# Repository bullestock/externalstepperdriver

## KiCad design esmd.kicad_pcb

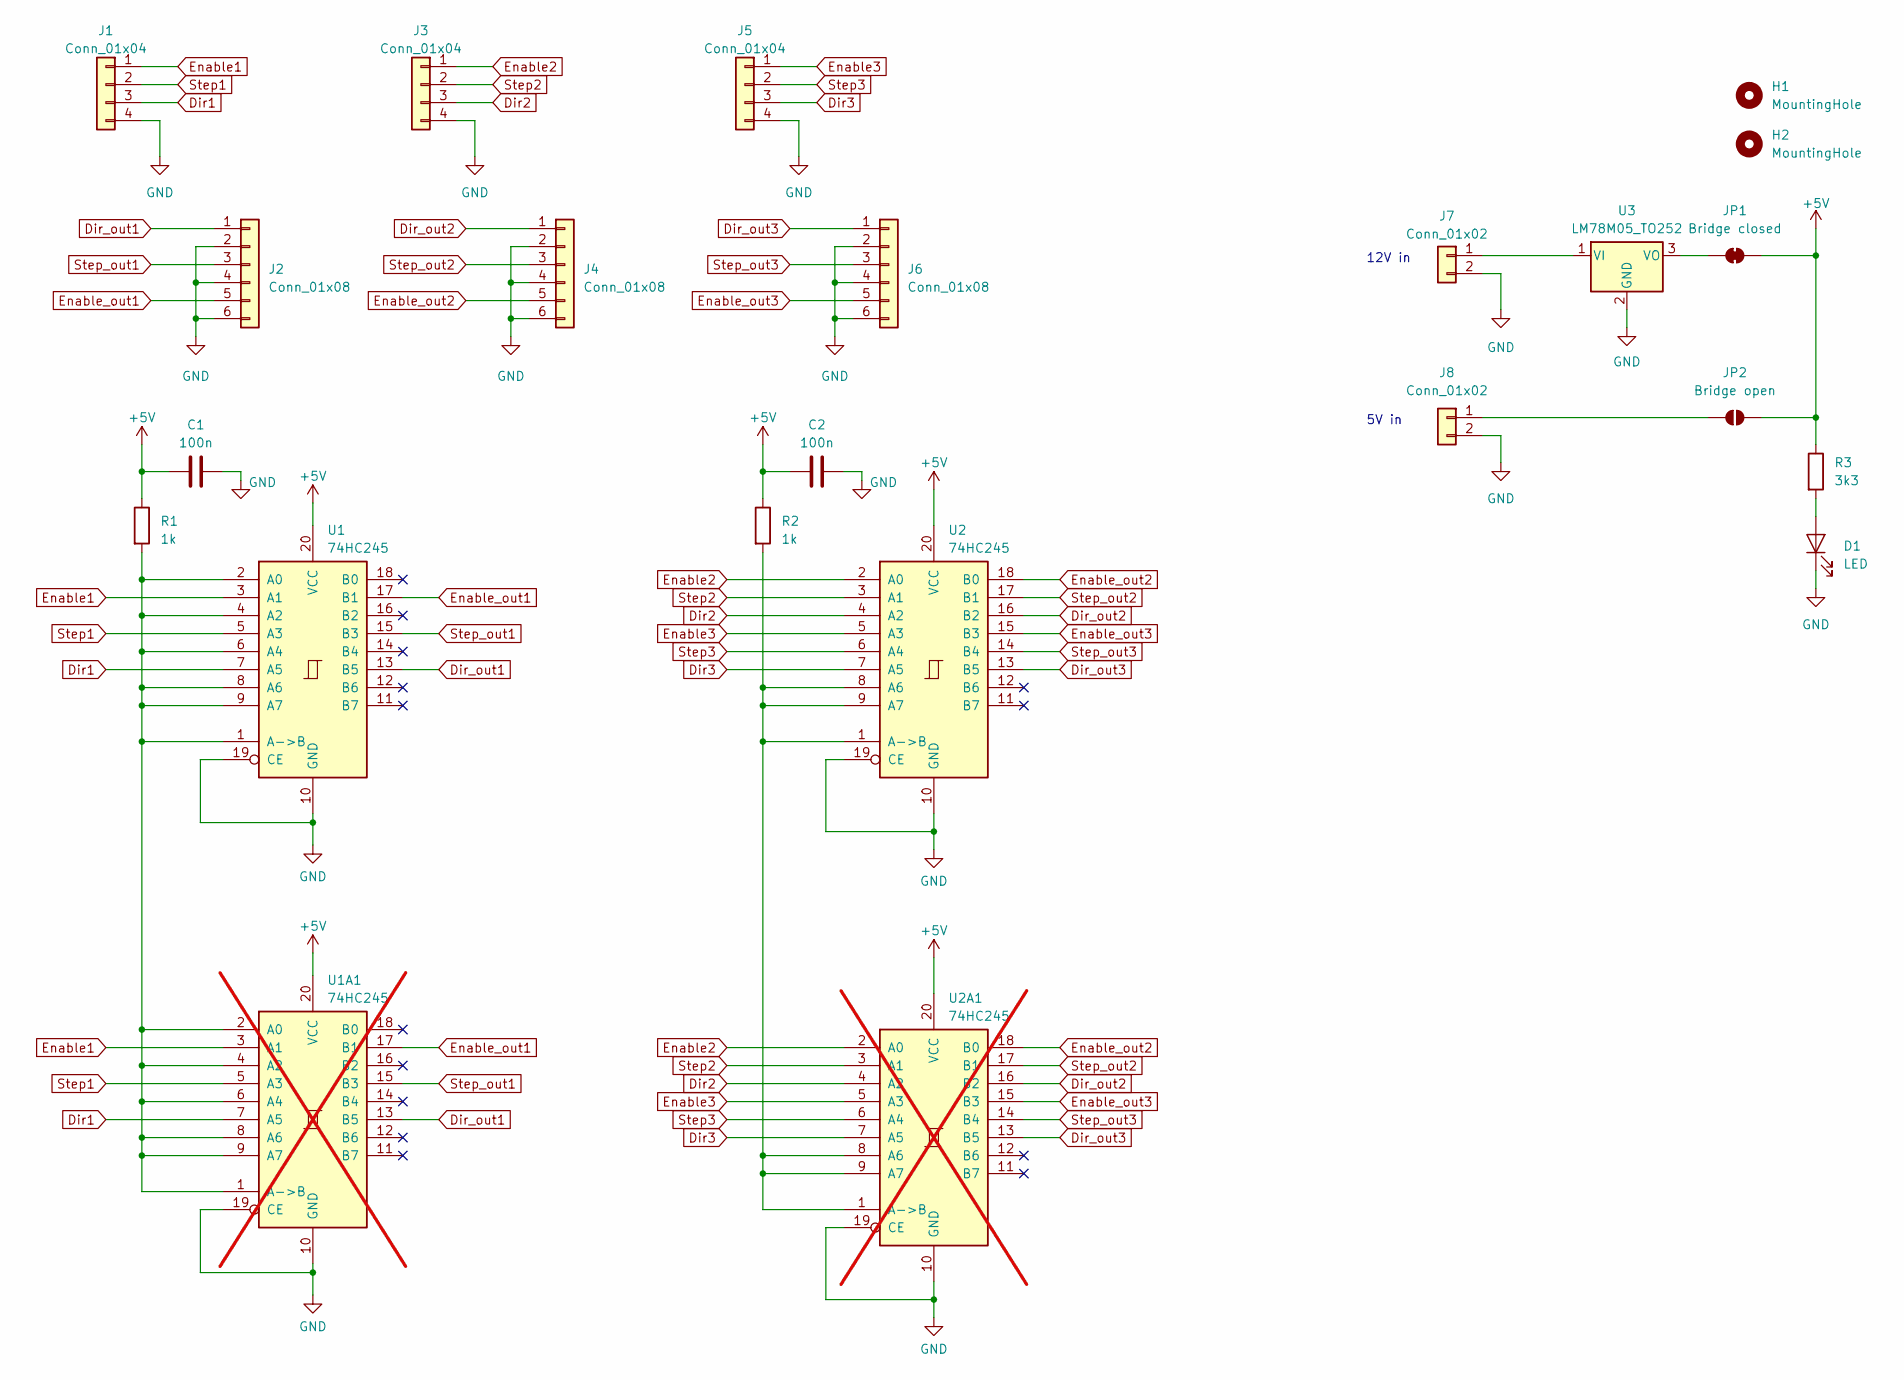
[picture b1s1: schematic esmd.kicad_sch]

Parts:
C1, C2: 100n; C_0603_1608Metric
D1: LED; LED_0603_1608Metric
H1, H2: MountingHole; MountingHole_3.2mm_M3
J1, J3, J5: Conn_01x04; JST_XH_B4B-XH-A_1x04_P2.50mm_Vertical
J2, J4, J6: Conn_01x08; JST_XH_B6B-XH-A_1x06_P2.50mm_Vertical
J7, J8: Conn_01x02; JST_XH_B2B-XH-A_1x02_P2.50mm_Vertical
JP1: Bridge closed; SolderJumper-2_P1.3mm_Bridged_RoundedPad1.0x1.5mm
JP2: Bridge open; SolderJumper-2_P1.3mm_Open_RoundedPad1.0x1.5mm
R1, R2: 1k; R_0603_1608Metric
R3: 3k3; R_0603_1608Metric
U1, U2: 74HC245; SO-20_5.3x12.6mm_P1.27mm
U1A1, U2A1: 74HC245; SOP-20_7.5x12.8mm_P1.27mm; not fitted
U3: LM78M05_TO252; TO-252-2

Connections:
+5V: C1.1, C2.1, JP1.1 (A), JP2.2 (B), R1.1, R2.1, R3.1, U1.20 (VCC), U1A1.20 (VCC), U2.20 (VCC), U2A1.20 (VCC)
Dir1: J1.3, U1.7 (A5), U1A1.7 (A5)
Dir2: J3.3, U2.4 (A2), U2A1.4 (A2)
Dir3: J5.3, U2.7 (A5), U2A1.7 (A5)
Dir_out1: J2.1, U1.13 (B5), U1A1.13 (B5)
Dir_out2: J4.1, U2.16 (B2), U2A1.16 (B2)
Dir_out3: J6.1, U2.13 (B5), U2A1.13 (B5)
Enable1: J1.1, U1.3 (A1), U1A1.3 (A1)
Enable2: J3.1, U2.2 (A0), U2A1.2 (A0)
Enable3: J5.1, U2.5 (A3), U2A1.5 (A3)
Enable_out1: J2.5, U1.17 (B1), U1A1.17 (B1)
Enable_out2: J4.5, U2.18 (B0), U2A1.18 (B0)
Enable_out3: J6.5, U2.15 (B3), U2A1.15 (B3)
GND: C1.2, C2.2, D1.1 (K), J1.4, J2.2, J2.4, J2.6, J3.4, J4.2, J4.4, J4.6, J5.4, J6.2, J6.4, J6.6, J7.2, J8.2, U1.10 (GND), U1.19 (CE), U1A1.10 (GND), U1A1.19 (CE), U2.10 (GND), U2.19 (CE), U2A1.10 (GND), U2A1.19 (CE), U3.2 (GND)
unnamed: D1.2 (A), R3.2
unnamed: J7.1, U3.1 (VI)
unnamed: J8.1, JP2.1 (A)
unnamed: JP1.2 (B), U3.3 (VO)
unnamed: R1.2, U1.1 (A->B), U1.2 (A0), U1.4 (A2), U1.6 (A4), U1.8 (A6), U1.9 (A7), U1A1.1 (A->B), U1A1.2 (A0), U1A1.4 (A2), U1A1.6 (A4), U1A1.8 (A6), U1A1.9 (A7)
unnamed: R2.2, U2.1 (A->B), U2.8 (A6), U2.9 (A7), U2A1.1 (A->B), U2A1.8 (A6), U2A1.9 (A7)
Step1: J1.2, U1.5 (A3), U1A1.5 (A3)
Step2: J3.2, U2.3 (A1), U2A1.3 (A1)
Step3: J5.2, U2.6 (A4), U2A1.6 (A4)
Step_out1: J2.3, U1.15 (B3), U1A1.15 (B3)
Step_out2: J4.3, U2.17 (B1), U2A1.17 (B1)
Step_out3: J6.3, U2.14 (B4), U2A1.14 (B4)

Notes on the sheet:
12V in
5V in

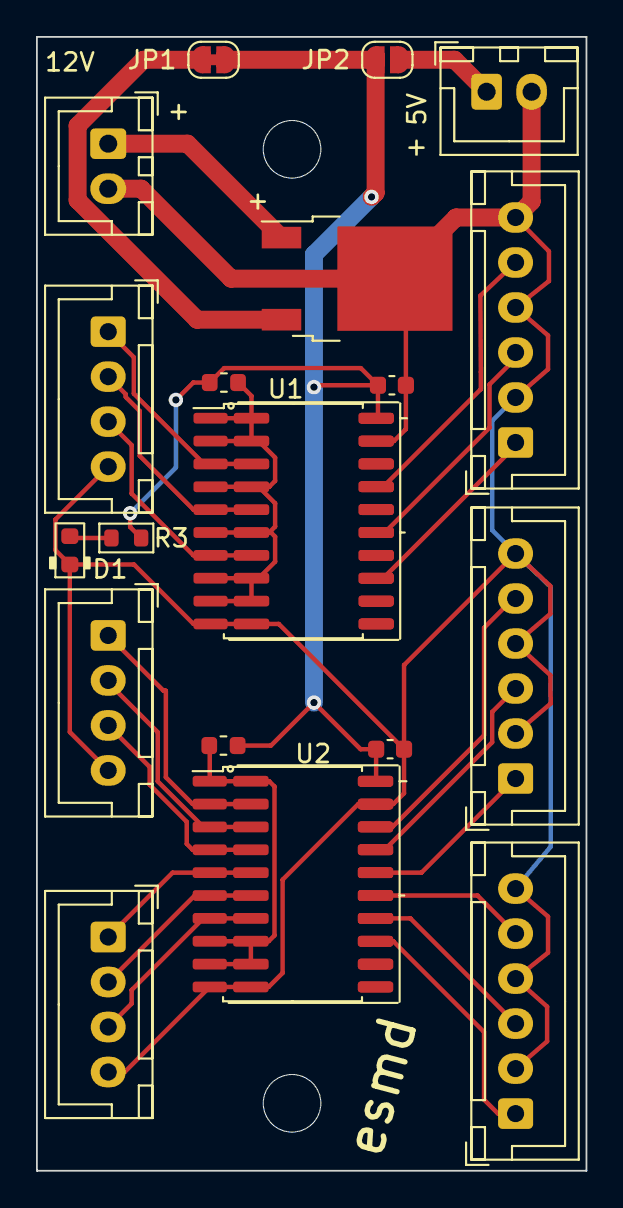
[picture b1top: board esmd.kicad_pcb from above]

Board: 2 copper layers, 30.5 x 63.0 mm, 23 parts (0 on the bottom side), 26 nets.

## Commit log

2023-08-31 Initial attempt.
2023-09-08 Make it triple.
2023-09-08 Fix footprints.
2023-09-21 Route.
2025-06-06 Add support for 5V supply.
2025-06-13 Add power LED.
2025-07-09 Use only two drivers.
2025-07-14 Add alternate footprints.
2025-07-29 Fix wrong 5V/12 labels.
